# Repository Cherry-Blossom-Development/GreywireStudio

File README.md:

# GreywireStudio

GreywireStudio is a line of guitar effects pedals from Cherry Blossom Development. The first series, **Linework**, is a set of pedals that work on their own or together under a phone-connected control pedal. See `General Concept.docx` for the overall product concept. `Linework Control Specification.docx` defines the rules every Linework pedal follows: the MIDI loop connecting them to Switchyard, the shared message map, presets and firmware updates.

## Tools

All tools are free:

| Tool | Purpose |
|------|---------|
| [KiCad](https://www.kicad.org/) | Schematic capture and PCB layout |
| [LTspice](https://www.analog.com/ltspice) | Circuit simulation (gain, clipping, tone response) |

## Layout

```
libraries/
  GreywireStudio.kicad_sym   # Shared KiCad symbols (e.g. 3PDT footswitch)
pedals/
  <pedal-name>/
    README.md   # Design notes, parts list, status
    *Product Document.docx  # Product definition
    kicad/      # KiCad project (schematic + PCB)
    sim/        # LTspice simulations (.asc)
```

## Pedals

| Pedal | Name | Type | Status |
|-------|------|------|--------|
| [Distortion](pedals/distortion/) | Flashover | Distortion / overdrive | Design |
| [Controller](pedals/controller/) | Switchyard | Control pedal (phone-connected) | Concept |
| [Controller with audio](pedals/controller-audio/) | Switchyard Audio | Control pedal plus digital effects | Planning |
| [Boost](pedals/boost/) | Tap Changer | Clean boost | Design |
| Phaser | Three Phase | Analog phaser | Idea |
| Tremolo | Rolling Blackout | Analog (optical) tremolo | Idea |
| Chorus | Double Circuit | Analog (bucket brigade) chorus / vibrato | Idea |

Product names are working names pending a trademark search (see `IP_RESEARCH.md`).

The public website is https://greywirestudio.com, kept in the [GreywireStudio-Website](https://github.com/Cherry-Blossom-Development/GreywireStudio-Website) repository.

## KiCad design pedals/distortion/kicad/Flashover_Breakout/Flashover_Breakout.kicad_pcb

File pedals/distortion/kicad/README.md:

# Distortion - KiCad Project

Create the KiCad project in this folder (File > New Project in KiCad).

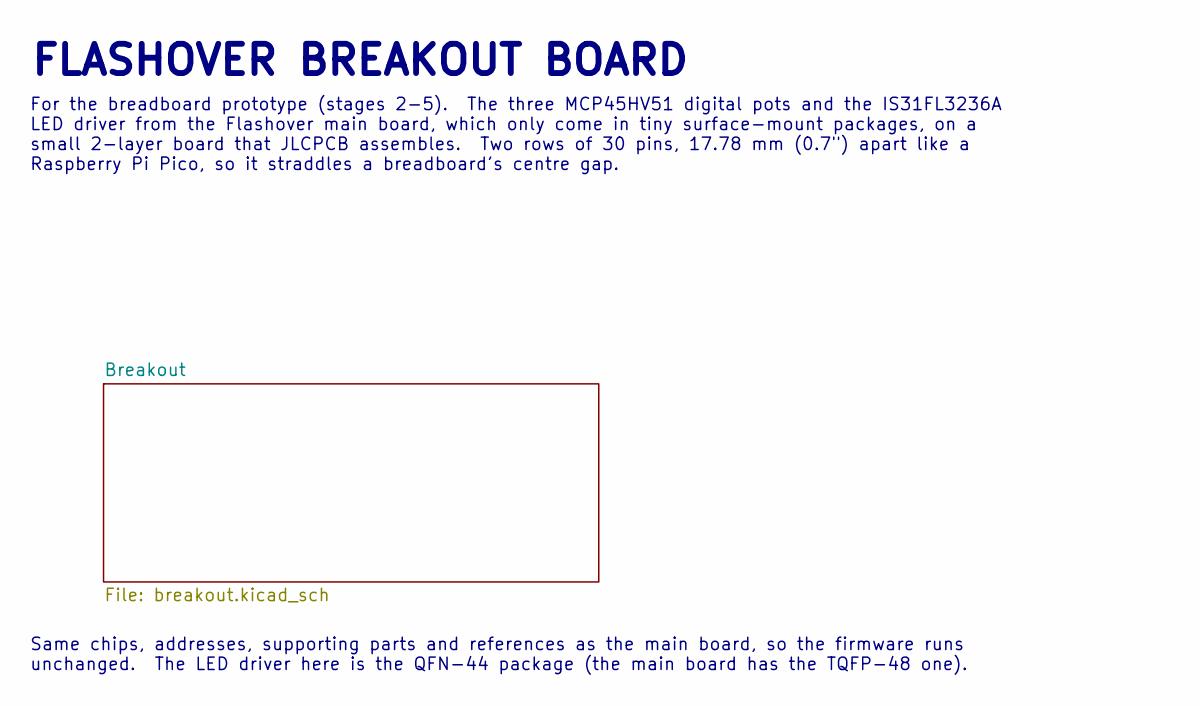
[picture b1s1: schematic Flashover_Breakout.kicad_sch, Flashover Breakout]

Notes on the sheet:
FLASHOVER BREAKOUT BOARD
For the breadboard prototype (stages 2-5). The three MCP45HV51 digital pots and the IS31FL3236A LED driver from the Flashover main board, which only come in tiny surface-mount packages, on a small 2-layer board that JLCPCB assembles. Two rows of 30 pins, 17.78 mm (0.7") apart like a Raspberry Pi Pi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
Same chips, addresses, supporting parts and references as the main board, so the firmware runs unchanged. The LED driver here is the QFN-44 package (the main board has the TQFP-48 one).

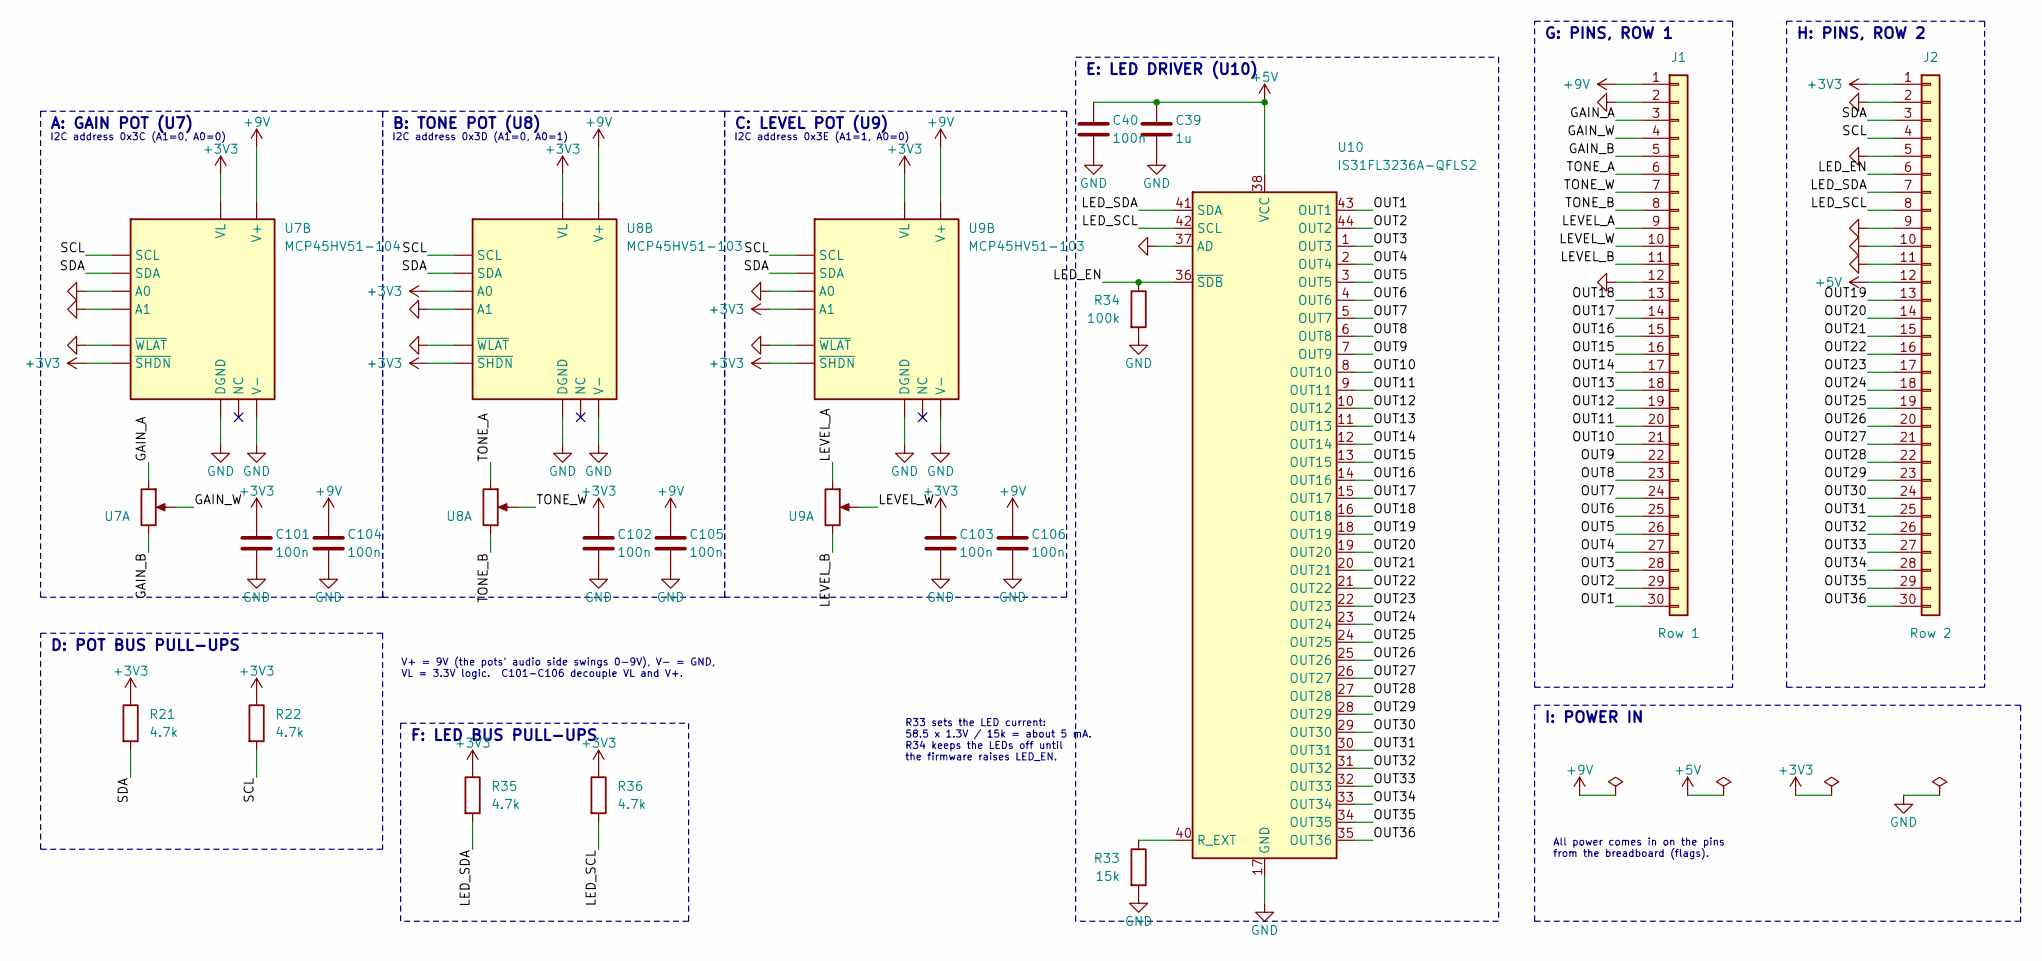
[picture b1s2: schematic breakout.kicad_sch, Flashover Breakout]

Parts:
C39: 1u; C_0603_1608Metric
C40, C101, C102, C103, C104, C105, C106: 100n; C_0603_1608Metric
J1: Row 1; PinHeader_1x30_P2.54mm_Vertical
J2: Row 2; PinHeader_1x30_P2.54mm_Vertical
R21, R22, R35, R36: 4.7k; R_0603_1608Metric
R33: 15k; R_0603_1608Metric
R34: 100k; R_0603_1608Metric
U7: MCP45HV51-104; TSSOP-14_4.4x5mm_P0.65mm
U8, U9: MCP45HV51-103; TSSOP-14_4.4x5mm_P0.65mm
U10: IS31FL3236A-QFLS2; QFN-44-1EP_5x5mm_P0.4mm_EP2.45x2.45mm

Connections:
+3V3: C101.1, C102.1, C103.1, J2.1, R21.1, R22.1, R35.1, R36.1, U7.1 (VL), U7.8 (~SHDN), U8.1 (VL), U8.5 (A0), U8.8 (~SHDN), U9.1 (VL), U9.3 (A1), U9.8 (~SHDN)
+5V: C39.1, C40.1, J2.12, U10.38 (VCC)
+9V: C104.1, C105.1, C106.1, J1.1, U7.14 (V+), U8.14 (V+), U9.14 (V+)
/Breakout/GAIN_A: J1.3, U7.13
/Breakout/GAIN_B: J1.5, U7.11
/Breakout/GAIN_W: J1.4, U7.12
/Breakout/LED_EN: J2.6, R34.1, U10.36 (~SDB)
/Breakout/LED_SCL: J2.8, R36.2, U10.42 (SCL)
/Breakout/LED_SDA: J2.7, R35.2, U10.41 (SDA)
/Breakout/LEVEL_A: J1.9, U9.13
/Breakout/LEVEL_B: J1.11, U9.11
/Breakout/LEVEL_W: J1.10, U9.12
/Breakout/OUT1: J1.30, U10.43 (OUT1)
/Breakout/OUT2: J1.29, U10.44 (OUT2)
/Breakout/OUT3: J1.28, U10.1 (OUT3)
/Breakout/OUT4: J1.27, U10.2 (OUT4)
/Breakout/OUT5: J1.26, U10.3 (OUT5)
/Breakout/OUT6: J1.25, U10.4 (OUT6)
/Breakout/OUT7: J1.24, U10.5 (OUT7)
/Breakout/OUT8: J1.23, U10.6 (OUT8)
/Breakout/OUT9: J1.22, U10.7 (OUT9)
/Breakout/OUT10: J1.21, U10.8 (OUT10)
/Breakout/OUT11: J1.20, U10.9 (OUT11)
/Breakout/OUT12: J1.19, U10.10 (OUT12)
/Breakout/OUT13: J1.18, U10.11 (OUT13)
/Breakout/OUT14: J1.17, U10.12 (OUT14)
/Breakout/OUT15: J1.16, U10.13 (OUT15)
/Breakout/OUT16: J1.15, U10.14 (OUT16)
/Breakout/OUT17: J1.14, U10.15 (OUT17)
/Breakout/OUT18: J1.13, U10.16 (OUT18)
/Breakout/OUT19: J2.13, U10.18 (OUT19)
/Breakout/OUT20: J2.14, U10.19 (OUT20)
/Breakout/OUT21: J2.15, U10.20 (OUT21)
/Breakout/OUT22: J2.16, U10.21 (OUT22)
/Breakout/OUT23: J2.17, U10.22 (OUT23)
/Breakout/OUT24: J2.18, U10.23 (OUT24)
/Breakout/OUT25: J2.19, U10.24 (OUT25)
/Breakout/OUT26: J2.20, U10.25 (OUT26)
/Breakout/OUT27: J2.21, U10.26 (OUT27)
/Breakout/OUT28: J2.22, U10.27 (OUT28)
/Breakout/OUT29: J2.23, U10.28 (OUT29)
/Breakout/OUT30: J2.24, U10.29 (OUT30)
/Breakout/OUT31: J2.25, U10.30 (OUT31)
/Breakout/OUT32: J2.26, U10.31 (OUT32)
/Breakout/OUT33: J2.27, U10.32 (OUT33)
/Breakout/OUT34: J2.28, U10.33 (OUT34)
/Breakout/OUT35: J2.29, U10.34 (OUT35)
/Breakout/OUT36: J2.30, U10.35 (OUT36)
/Breakout/SCL: J2.4, R22.2, U7.2 (SCL), U8.2 (SCL), U9.2 (SCL)
/Breakout/SDA: J2.3, R21.2, U7.4 (SDA), U8.4 (SDA), U9.4 (SDA)
/Breakout/TONE_A: J1.6, U8.13
/Breakout/TONE_B: J1.8, U8.11
/Breakout/TONE_W: J1.7, U8.12
GND: C39.2, C40.2, C101.2, C102.2, C103.2, C104.2, C105.2, C106.2, J1.2, J1.12, J2.2, J2.5, J2.9, J2.10, J2.11, R33.2, R34.2, U7.3 (A1), U7.5 (A0), U7.6 (~WLAT), U7.9 (DGND), U7.10 (V-), U8.3 (A1), U8.6 (~WLAT), U8.9 (DGND), U8.10 (V-), U9.5 (A0), U9.6 (~WLAT), U9.9 (DGND), U9.10 (V-), U10.17 (GND), U10.37 (AD), U10.39 (GND), U10.45 (GND)
unnamed: R33.1, U10.40 (R_EXT)

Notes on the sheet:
A: GAIN POT (U7)
I2C address 0x3C (A1=0, A0=0)
B: TONE POT (U8)
I2C address 0x3D (A1=0, A0=1)
C: LEVEL POT (U9)
I2C address 0x3E (A1=1, A0=0)
D: POT BUS PULL-UPS
V+ = 9V (the pots' audio side swings 0-9V), V- = GND, VL = 3.3V logic. C101-C106 decouple VL and V+.
E: LED DRIVER (U10)
R33 sets the LED current: 58.5 x 1.3V / 15k = about 5 mA. R34 keeps the LEDs off until the firmware raises LED_EN.
F: LED BUS PULL-UPS
G: PINS, ROW 1
H: PINS, ROW 2
I: POWER IN
All power comes in on the pins from the breadboard (flags).

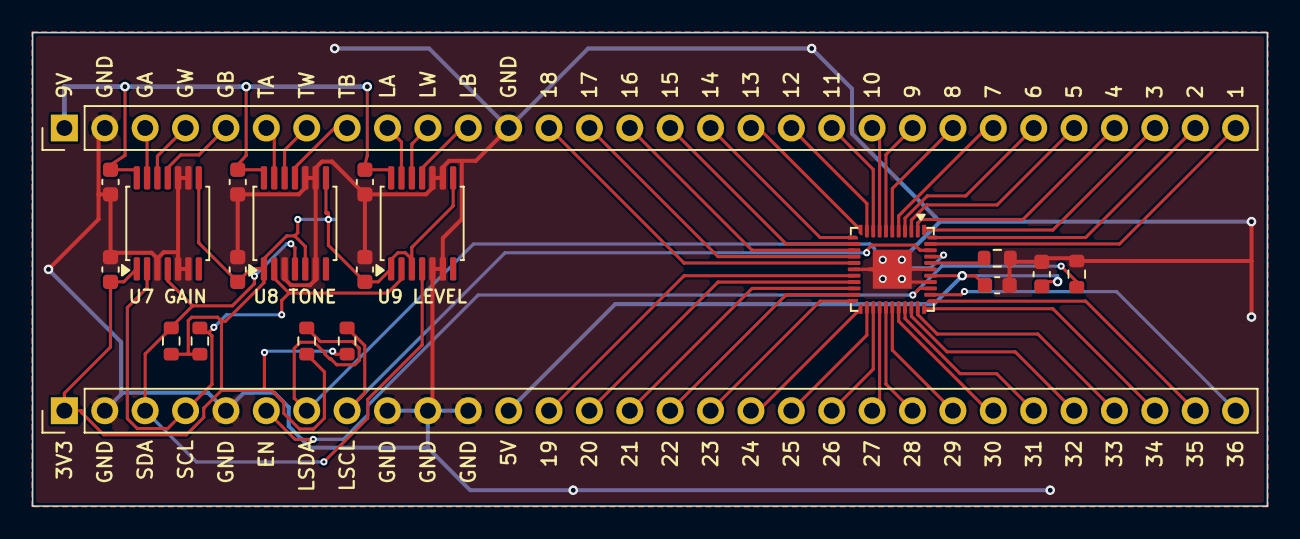
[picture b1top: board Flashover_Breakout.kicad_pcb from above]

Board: 2 copper layers, 77.7 x 29.8 mm, 20 parts (0 on the bottom side), 55 nets.

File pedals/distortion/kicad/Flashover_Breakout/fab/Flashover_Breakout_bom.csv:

Comment,Designator,Footprint,LCSC Part #
100k 1% 0603,R34,R_0603_1608Metric,C25803
100nF 50V X7R 0603,"C40,C101,C102,C103,C104,C105,C106",C_0603_1608Metric,C14663
15k 1% 0603,R33,R_0603_1608Metric,C22809
1uF 25V X5R 0603,C39,C_0603_1608Metric,C15849
4.7k 1% 0603,"R21,R22,R35,R36",R_0603_1608Metric,C23162
IS31FL3236A-QFLS2-TR,U10,QFN-44-1EP_5x5mm_P0.4mm_EP2.45x2.45mm,C246443
MCP45HV51-103E/ST,"U8,U9",TSSOP-14_4.4x5mm_P0.65mm,C637117
MCP45HV51-104E/ST,U7,TSSOP-14_4.4x5mm_P0.65mm,C637118

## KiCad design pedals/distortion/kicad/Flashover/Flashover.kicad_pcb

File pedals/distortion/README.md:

# Distortion Pedal (Flashover)

The first GreywireStudio pedal: an analog distortion / overdrive in the Linework series, with gain, tone and level controls. It works on its own or controlled by the Switchyard control pedal. See `Flashover Product Document.docx`.

The design files still use the internal name GS1.

## Folders

- `kicad/` - KiCad project (schematic and PCB layout)
- `sim/` - LTspice simulations of the circuit
- `firmware/` - firmware for the RP2040 (started November 2026; not yet run on hardware)

## Status

Design - circuit not yet started.

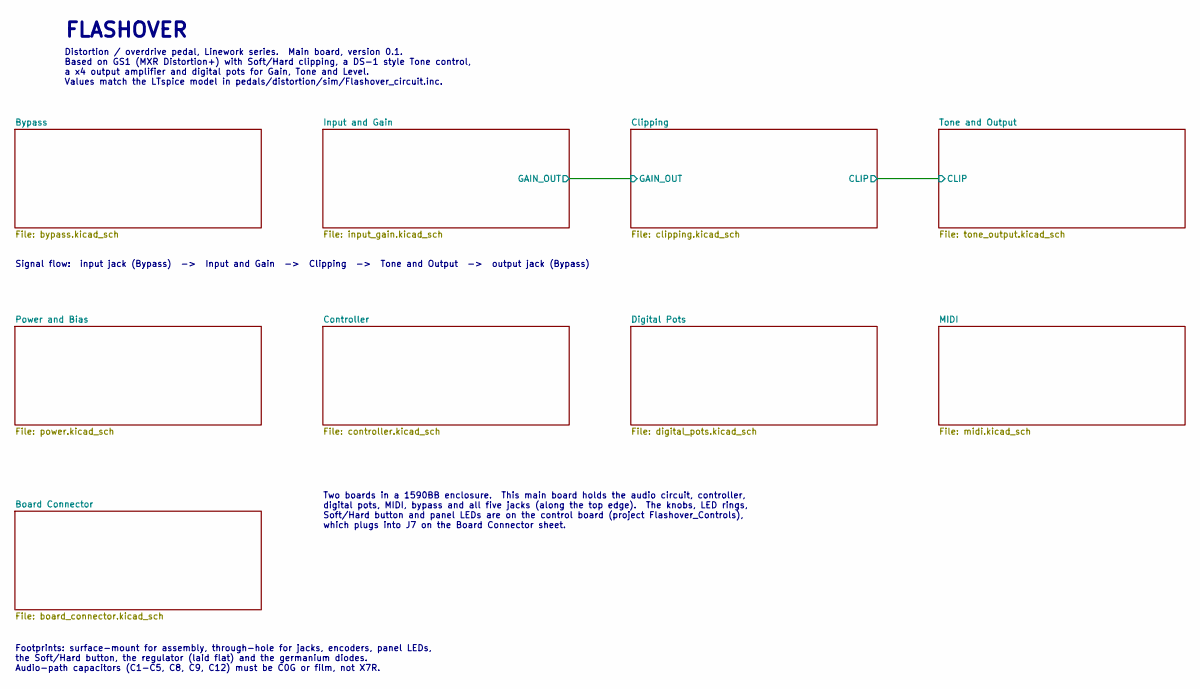
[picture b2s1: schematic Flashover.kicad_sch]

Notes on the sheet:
FLASHOVER
Distortion / overdrive pedal, Linework series. Main board, version 0.1. Based on GS1 (MXR Distortion+) with Soft/Hard clipping, a DS-1 style Tone control, a x4 output amplifier and digital pots for Gain, Tone and Level. Values match the LTspice model in pedals/distortion/sim/Flashover_circuit.inc.
Signal flow: input jack (Bypass) -> Input and Gain -> Clipping -> Tone and Output -> output jack (Bypass)
Two boards in a 1590BB enclosure. This main board holds the audio circuit, controller, digital pots, MIDI, bypass and all five jacks (along the top edge). The knobs, LED rings, Soft/Hard button and panel LEDs are on the control board (project Flashover_Controls), which plugs into J7 on the Board Co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
Footprints: surface-mount for assembly, through-hole for jacks, encoders, panel LEDs, the Soft/Hard button, the regulator (laid flat) and the germanium diodes. Audio-path capacitors (C1-C5, C8, C9, C12) must be C0G or film, not X7R.

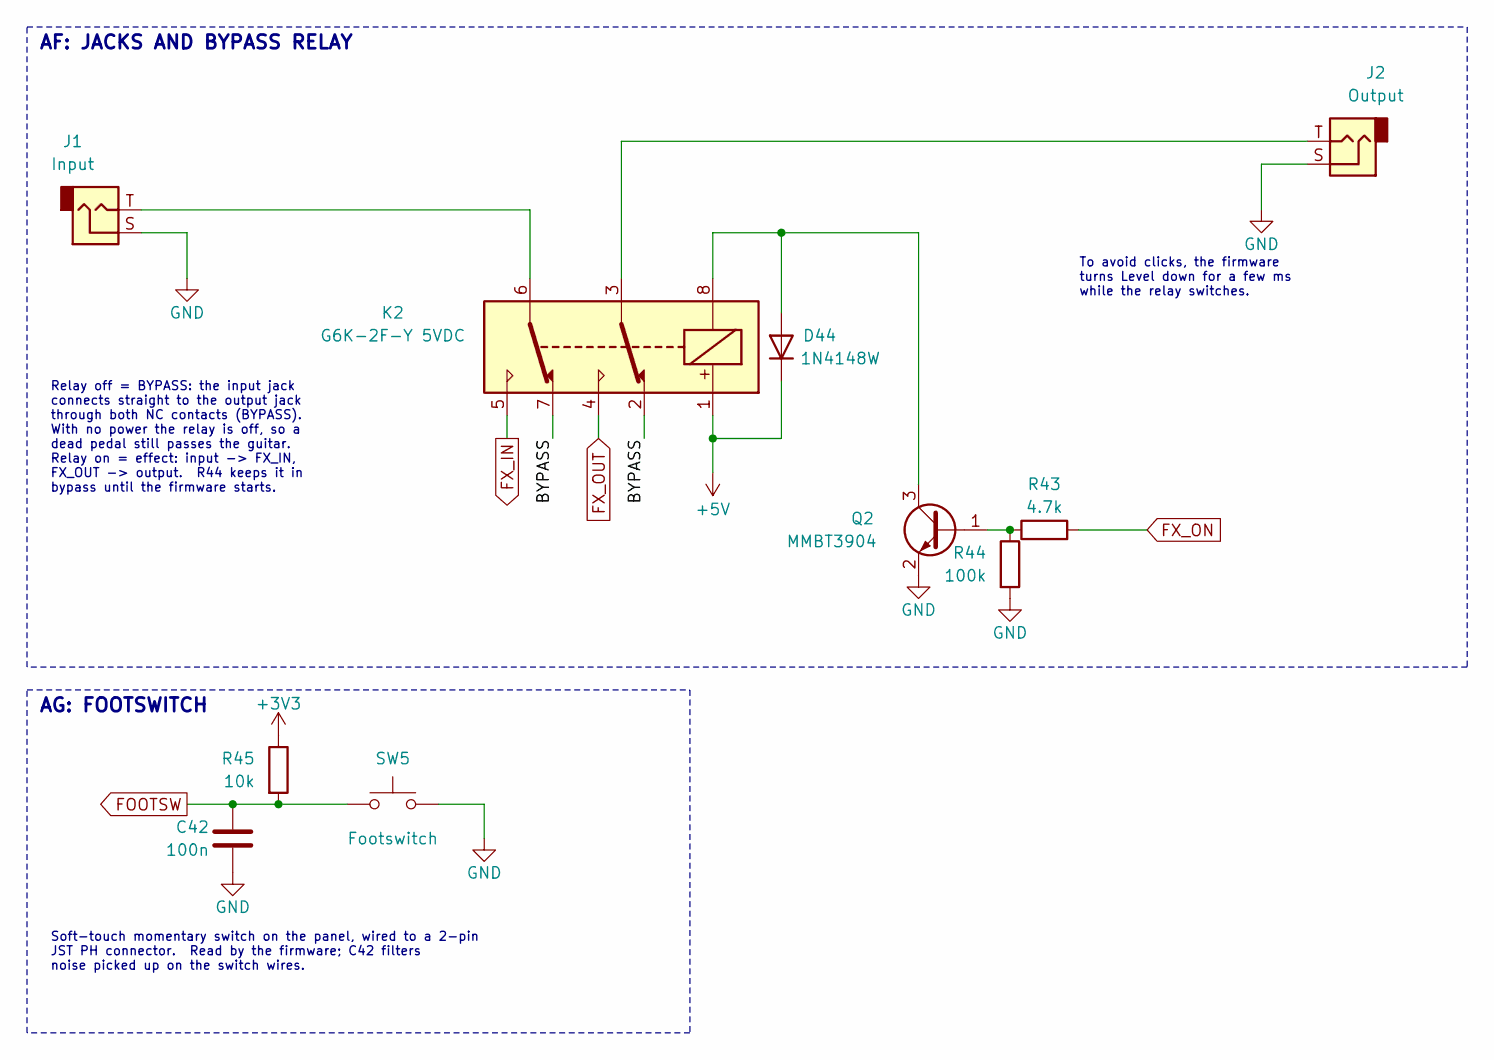
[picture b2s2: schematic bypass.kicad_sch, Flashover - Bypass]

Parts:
C42: 100n; C_0805_2012Metric
D44: 1N4148W; D_SOD-123
J1: Input; Jack_6.35mm_Neutrik_NRJ4HF_Horizontal
J2: Output; Jack_6.35mm_Neutrik_NRJ4HF_Horizontal
K2: G6K-2F-Y 5VDC; Relay_DPDT_Omron_G6K-2F-Y
Q2: MMBT3904; SOT-23
R43: 4.7k; R_0805_2012Metric
R44: 100k; R_0805_2012Metric
R45: 10k; R_0805_2012Metric
SW5: Footswitch; JST_PH_S2B-PH-K_1x02_P2.00mm_Horizontal

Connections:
+3V3: R45.1; also elsewhere on the board
+5V: D44.1 (K), K2.1; also elsewhere on the board
/Bypass/BYPASS: K2.2, K2.7
FOOTSW: C42.1, R45.2, SW5.1; also elsewhere on the board
FX_IN: K2.5; also elsewhere on the board
FX_ON: R43.2; also elsewhere on the board
FX_OUT: K2.4; also elsewhere on the board
GND: C42.2, J1.S, J2.S, Q2.2 (E), R44.2, SW5.2; also elsewhere on the board
unnamed: D44.2 (A), K2.8, Q2.3 (C)
unnamed: J1.T, K2.6
unnamed: J2.T, K2.3
unnamed: Q2.1 (B), R43.1, R44.1

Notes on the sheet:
AF: JACKS AND BYPASS RELAY
AG: FOOTSWITCH
Relay off = BYPASS: the input jack connects straight to the output jack through both NC contacts (BYPASS). With no power the relay is off, so a dead pedal still passes the guitar. Relay on = effect: input -> FX_IN, FX_OUT -> output. R44 keeps it in bypass until the firmware starts.
To avoid clicks, the firmware turns Level down for a few ms while the relay switches.
Soft-touch momentary switch on the panel, wired to a 2-pin JST PH connector. Read by the firmware; C42 filters noise picked up on the switch wires.

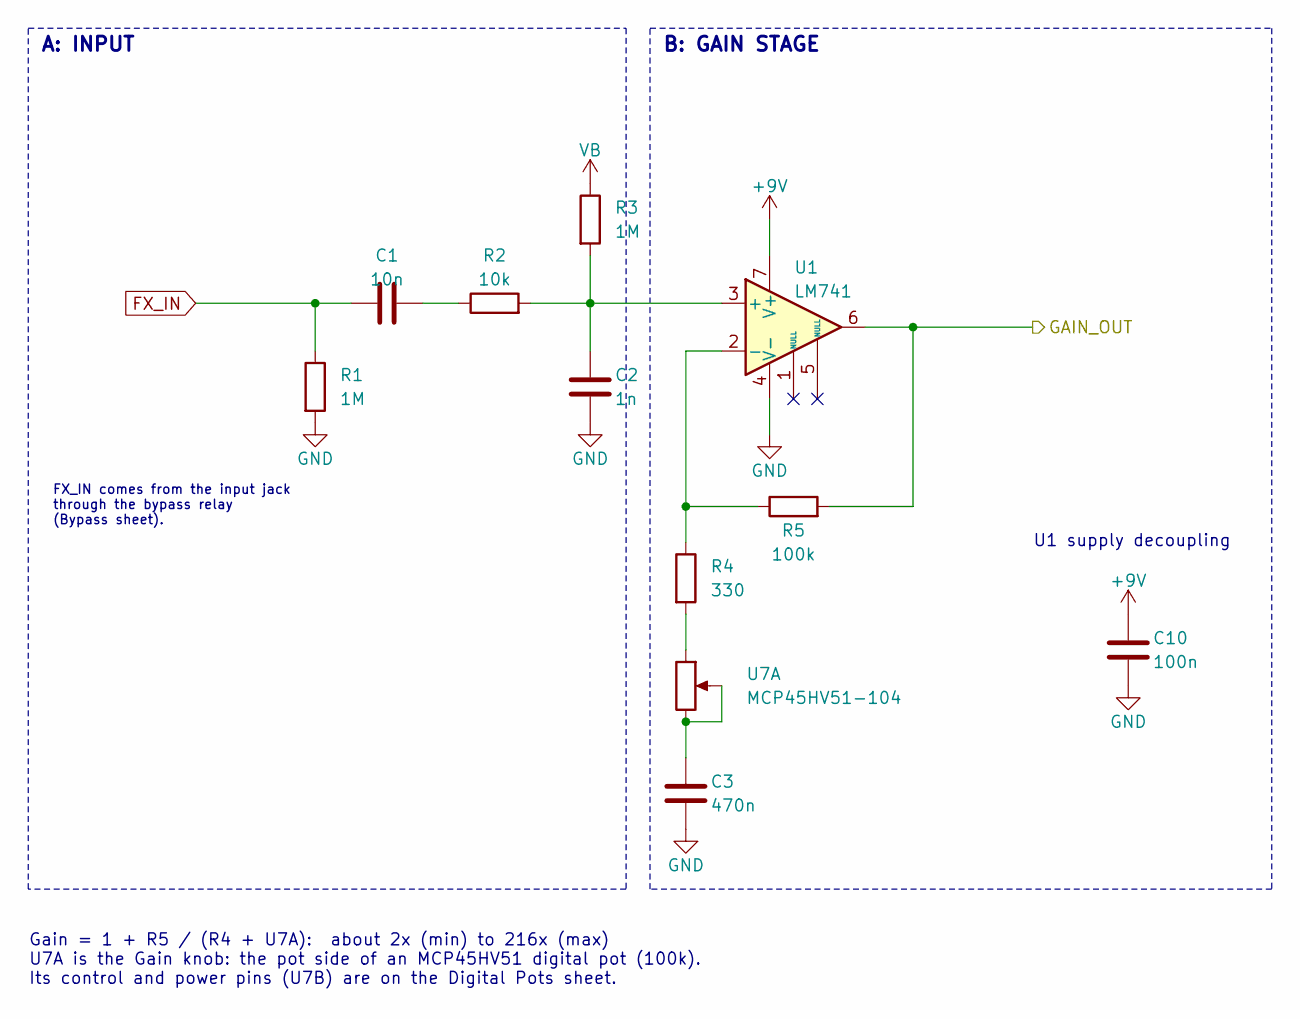
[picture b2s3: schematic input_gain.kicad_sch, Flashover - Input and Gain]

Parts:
C1: 10n; C_1206_3216Metric
C2: 1n; C_0805_2012Metric
C3: 470n; C_1210_3225Metric
C10: 100n; C_0805_2012Metric
R1, R3: 1M; R_0805_2012Metric
R2: 10k; R_0805_2012Metric
R4: 330; R_0805_2012Metric
R5: 100k; R_0805_2012Metric
U1: LM741; SOIC-8_3.9x4.9mm_P1.27mm
U7: MCP45HV51-104; TSSOP-14_4.4x5mm_P0.65mm

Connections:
+9V: C10.1, U1.7 (V+); also elsewhere on the board
/Clipping/GAIN_OUT: R5.2, U1.6; also elsewhere on the board
FX_IN: C1.1, R1.1; also elsewhere on the board
GND: C2.2, C3.2, C10.2, R1.2, U1.4 (V-); also elsewhere on the board
unnamed: C1.2, R2.1
unnamed: C3.1, U7.11, U7.12
unnamed: R4.2, U7.13
unnamed: C2.1, R2.2, R3.2, U1.3 (+)
unnamed: R4.1, R5.1, U1.2 (-)
VB: R3.1; also elsewhere on the board

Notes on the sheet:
A: INPUT
B: GAIN STAGE
FX_IN comes from the input jack through the bypass relay (Bypass sheet).
U1 supply decoupling
Gain = 1 + R5 / (R4 + U7A): about 2x (min) to 216x (max) U7A is the Gain knob: the pot side of an MCP45HV51 digital pot (100k). Its control and power pins (U7B) are on the Digital Pots sheet.

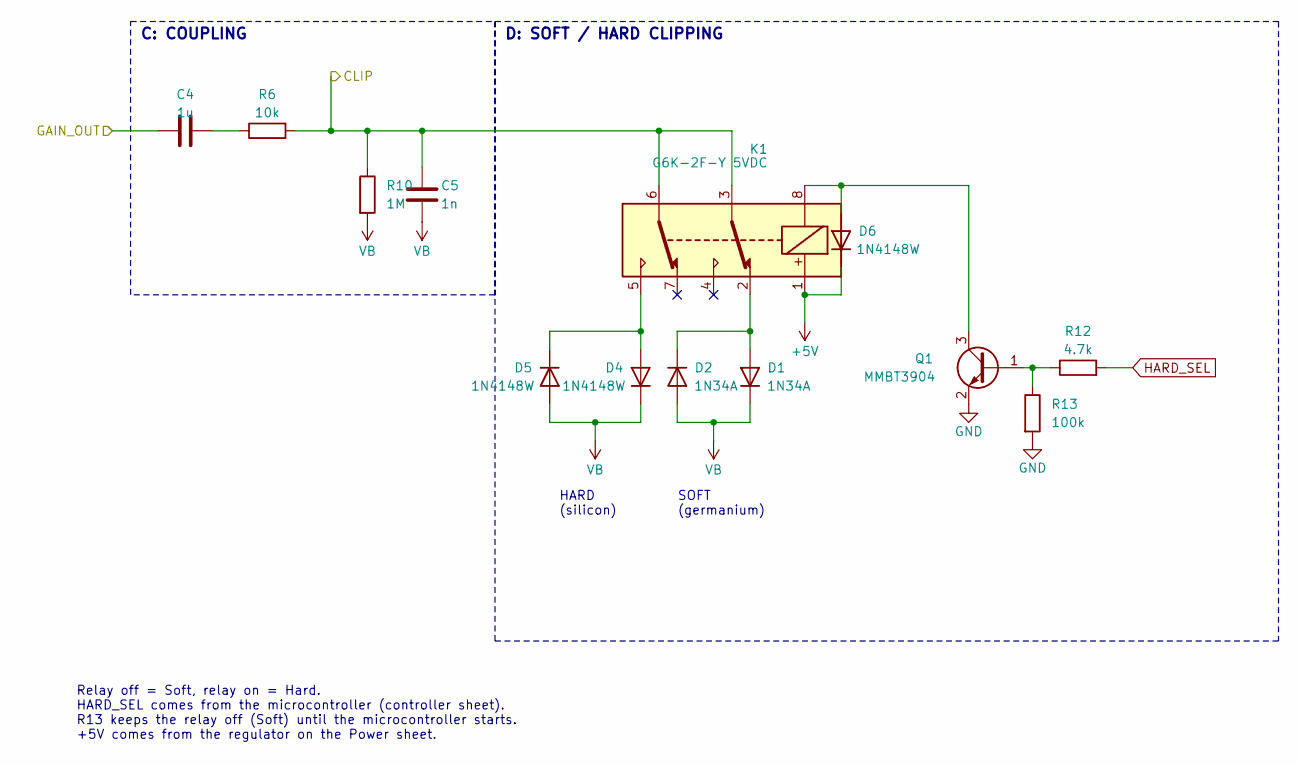
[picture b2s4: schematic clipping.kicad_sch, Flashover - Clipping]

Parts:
C4: 1u; C_1210_3225Metric
C5: 1n; C_0805_2012Metric
D1, D2: 1N34A; D_DO-35_SOD27_P7.62mm_Horizontal
D4, D5, D6: 1N4148W; D_SOD-123
K1: G6K-2F-Y 5VDC; Relay_DPDT_Omron_G6K-2F-Y
Q1: MMBT3904; SOT-23
R6: 10k; R_0805_2012Metric
R10: 1M; R_0805_2012Metric
R12: 4.7k; R_0805_2012Metric
R13: 100k; R_0805_2012Metric

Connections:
+5V: D6.1 (K), K1.1; also elsewhere on the board
/Clipping/CLIP: C5.1, K1.3, K1.6, R6.2, R10.1; also elsewhere on the board
/Clipping/GAIN_OUT: C4.1; also elsewhere on the board
GND: Q1.2 (E), R13.2; also elsewhere on the board
HARD_SEL: R12.2; also elsewhere on the board
unnamed: C4.2, R6.1
unnamed: D1.2 (A), D2.1 (K), K1.2
unnamed: D4.2 (A), D5.1 (K), K1.5
unnamed: D6.2 (A), K1.8, Q1.3 (C)
unnamed: Q1.1 (B), R12.1, R13.1
VB: C5.2, D1.1 (K), D2.2 (A), D4.1 (K), D5.2 (A), R10.2; also elsewhere on the board

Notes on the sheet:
C: COUPLING
D: SOFT / HARD CLIPPING
SOFT (germanium)
HARD (silicon)
Relay off = Soft, relay on = Hard. HARD_SEL comes from the microcontroller (controller sheet). R13 keeps the relay off (Soft) until the microcontroller starts. +5V comes from the regulator on the Power sheet.

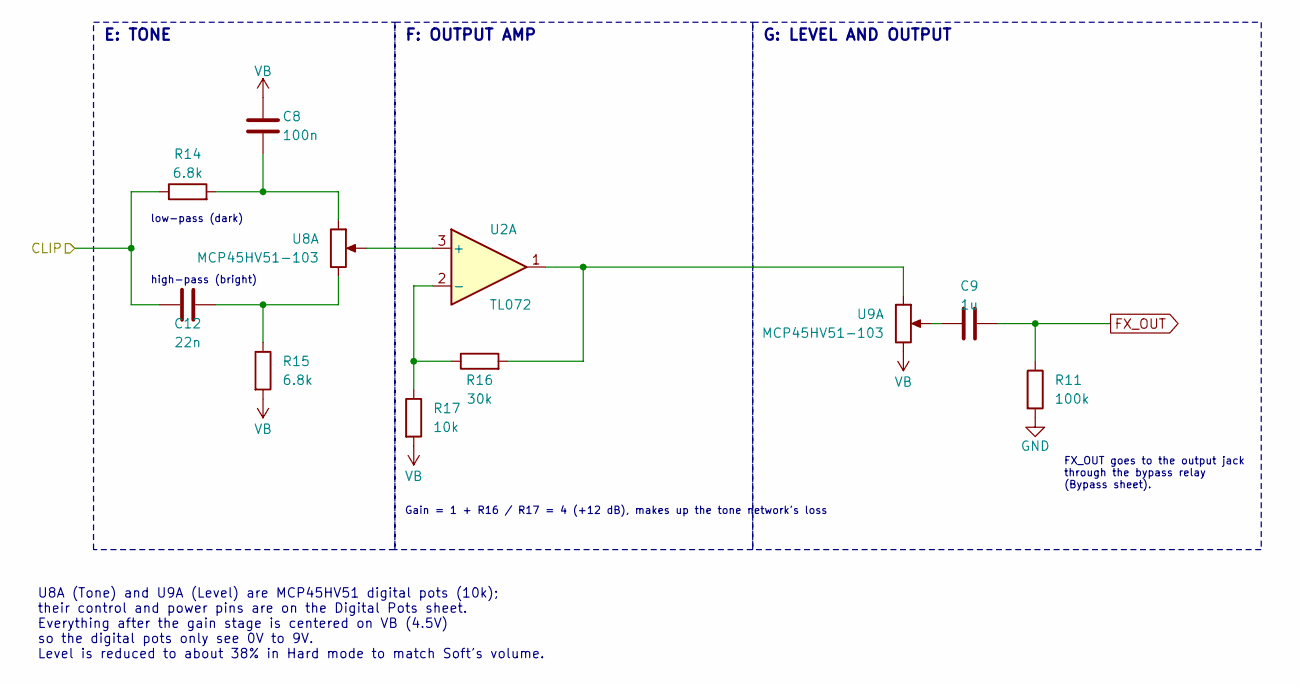
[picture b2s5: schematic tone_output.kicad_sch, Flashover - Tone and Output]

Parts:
C8: 100n; C_1206_3216Metric
C9: 1u; C_1210_3225Metric
C12: 22n; C_1206_3216Metric
R11: 100k; R_0805_2012Metric
R14, R15: 6.8k; R_0805_2012Metric
R16: 30k; R_0805_2012Metric
R17: 10k; R_0805_2012Metric
U2: TL072; SOIC-8_3.9x4.9mm_P1.27mm
U8, U9: MCP45HV51-103; TSSOP-14_4.4x5mm_P0.65mm

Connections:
/Clipping/CLIP: C12.1, R14.1; also elsewhere on the board
FX_OUT: C9.2, R11.1; also elsewhere on the board
GND: R11.2; also elsewhere on the board
unnamed: C8.2, R14.2, U8.13
unnamed: C9.1, U9.12
unnamed: C12.2, R15.1, U8.11
unnamed: R16.2, U2.1, U9.13
unnamed: U2.3 (+), U8.12
unnamed: R16.1, R17.1, U2.2 (-)
VB: C8.1, R15.2, R17.2, U9.11; also elsewhere on the board

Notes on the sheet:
E: TONE
F: OUTPUT AMP
G: LEVEL AND OUTPUT
low-pass (dark)
high-pass (bright)
FX_OUT goes to the output jack through the bypass relay (Bypass sheet).
Gain = 1 + R16 / R17 = 4 (+12 dB), makes up the tone network's loss
U8A (Tone) and U9A (Level) are MCP45HV51 digital pots (10k); their control and power pins are on the Digital Pots sheet. Everything after the gain stage is centered on VB (4.5V) so the digital pots only see 0V to 9V. Level is reduced to about 38% in Hard mode to match Soft's volume.

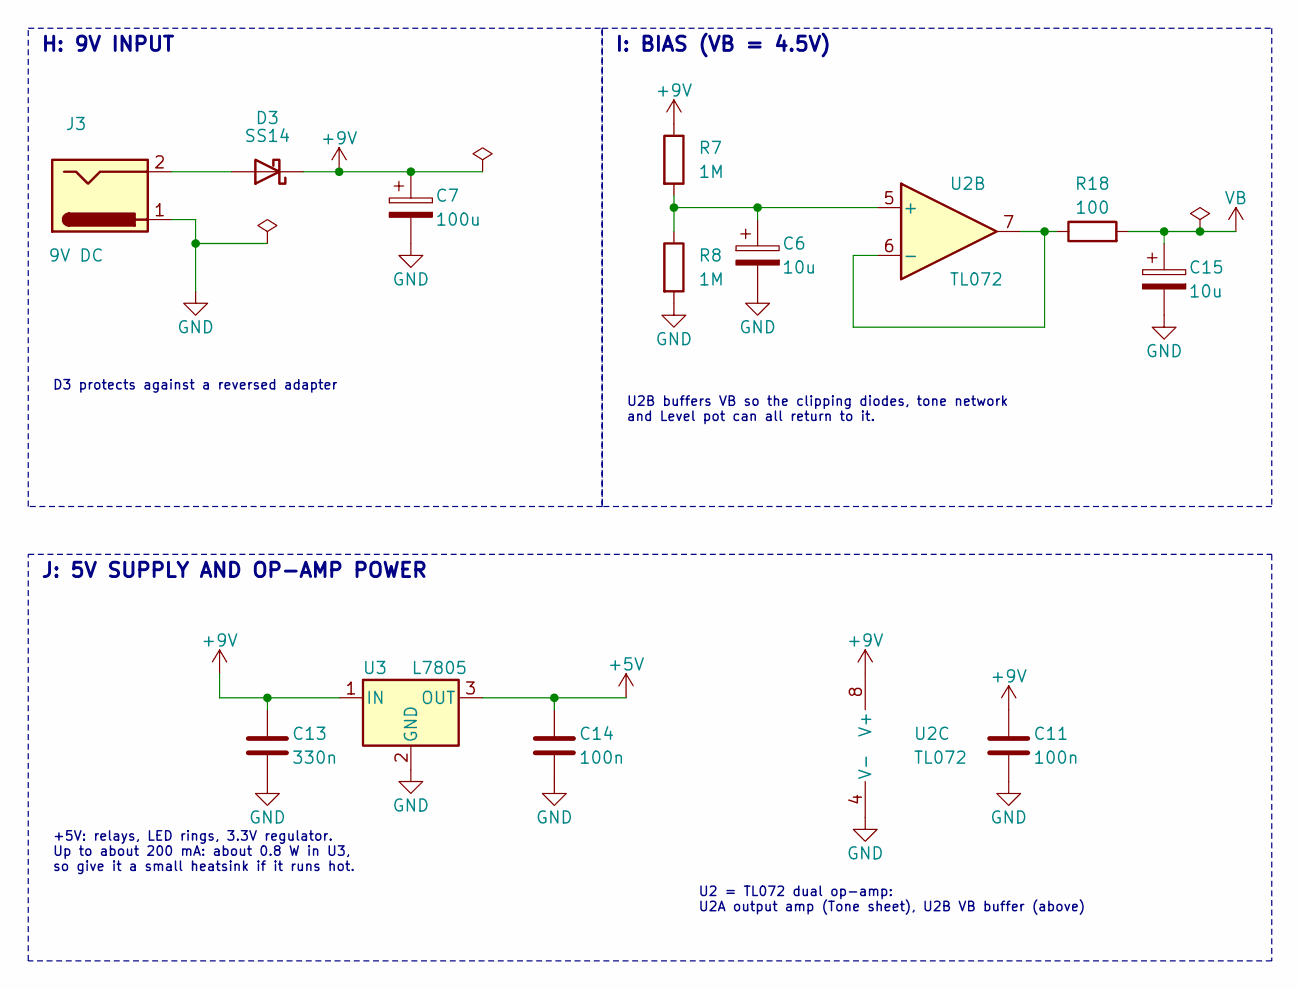
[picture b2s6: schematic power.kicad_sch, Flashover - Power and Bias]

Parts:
C6, C15: 10u; CP_Elec_5x5.4
C7: 100u; CP_Elec_6.3x5.4
C11, C14: 100n; C_0805_2012Metric
C13: 330n; C_0805_2012Metric
D3: SS14; D_SMA
J3: 9V DC; BarrelJack_CUI_PJ-102AH_Horizontal
R7, R8: 1M; R_0805_2012Metric
R18: 100; R_0805_2012Metric
U2: TL072; SOIC-8_3.9x4.9mm_P1.27mm
U3: L7805; TO-220-3_Horizontal_TabDown

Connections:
+5V: C14.1, U3.3 (OUT); also elsewhere on the board
+9V: C7.1, C11.1, C13.1, D3.1 (K), R7.1, U2.8 (V+), U3.1 (IN); also elsewhere on the board
GND: C6.2, C7.2, C11.2, C13.2, C14.2, C15.2, J3.1, R8.2, U2.4 (V-), U3.2 (GND); also elsewhere on the board
unnamed: D3.2 (A), J3.2
unnamed: C6.1, R7.2, R8.1, U2.5 (+)
unnamed: R18.1, U2.6 (-), U2.7
VB: C15.1, R18.2; also elsewhere on the board

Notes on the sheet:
H: 9V INPUT
I: BIAS (VB = 4.5V)
J: 5V SUPPLY AND OP-AMP POWER
D3 protects against a reversed adapter
U2B buffers VB so the clipping diodes, tone network and Level pot can all return to it.
+5V: relays, LED rings, 3.3V regulator. Up to about 200 mA: about 0.8 W in U3, so give it a small heatsink if it runs hot.
U2 = TL072 dual op-amp: U2A output amp (Tone sheet), U2B VB buffer (above)

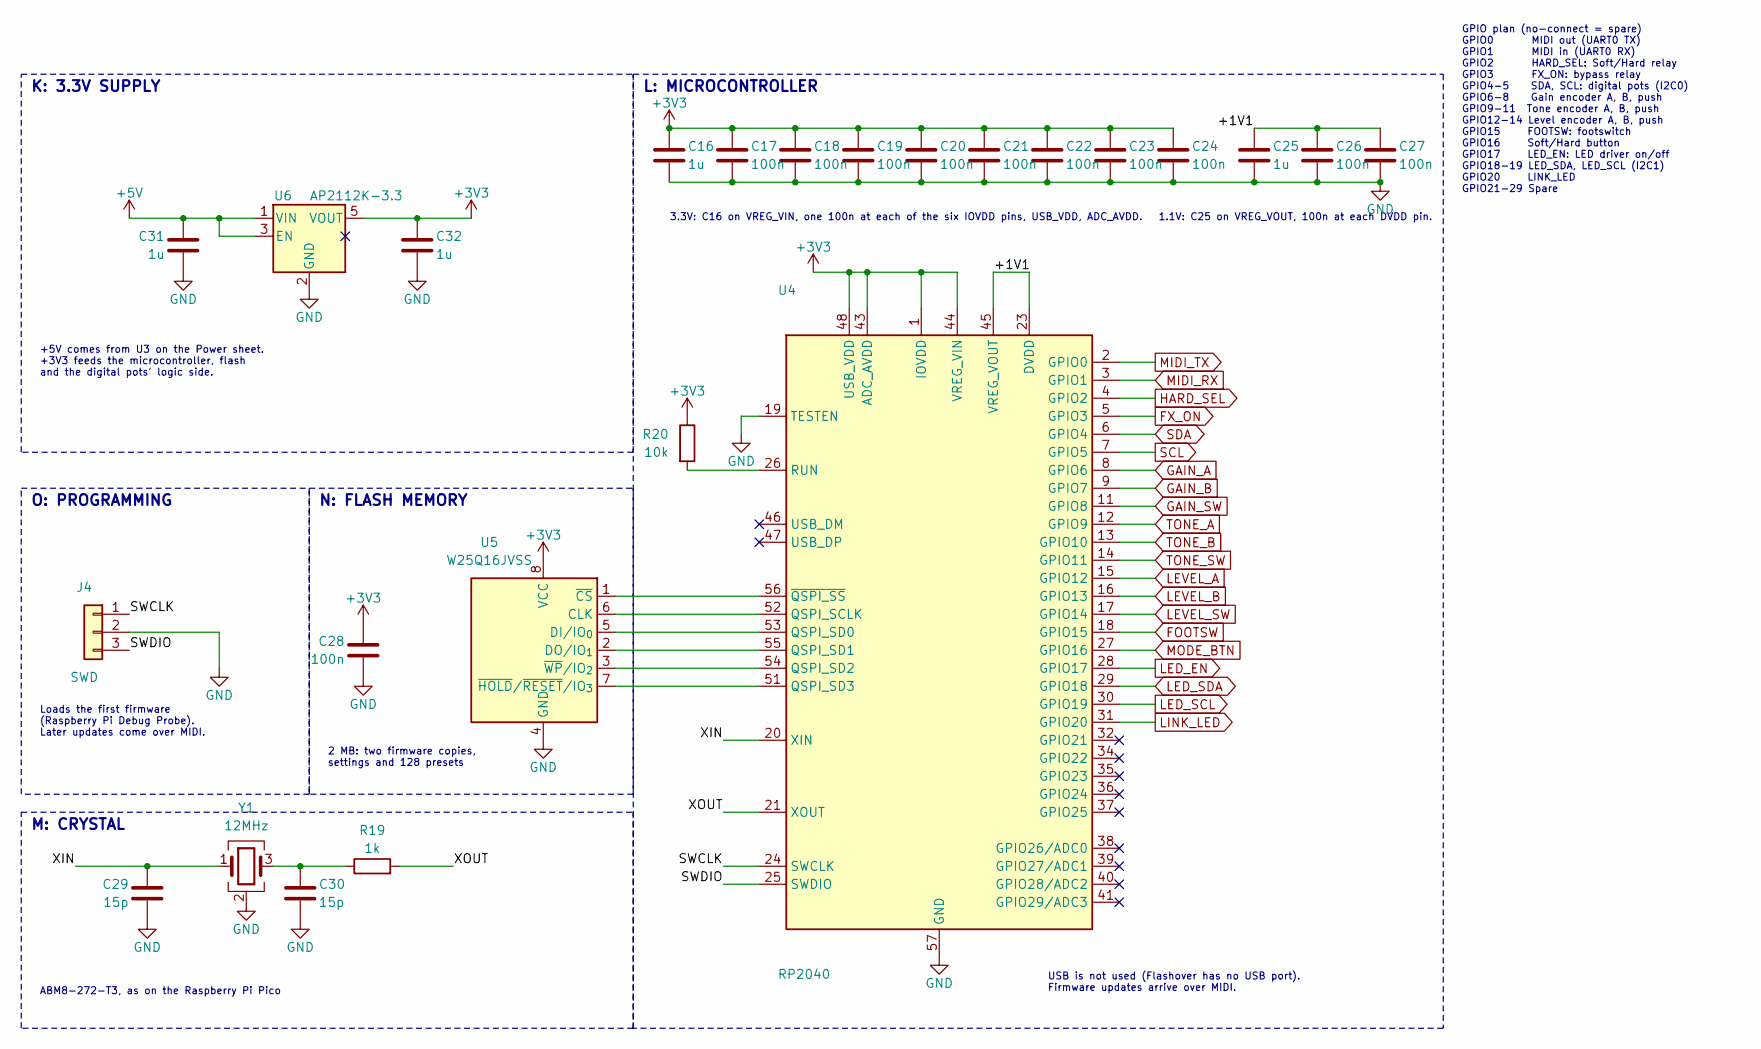
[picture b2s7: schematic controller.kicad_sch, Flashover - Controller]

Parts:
C16, C25, C31, C32: 1u; C_0805_2012Metric
C17, C18, C19, C20, C21, C22, C23, C24, C26, C27, C28: 100n; C_0805_2012Metric
C29, C30: 15p; C_0805_2012Metric
J4: SWD; JST_SH_SM03B-SRSS-TB_1x03-1MP_P1.00mm_Horizontal
R19: 1k; R_0805_2012Metric
R20: 10k; R_0805_2012Metric
U4: RP2040; QFN-56-1EP_7x7mm_P0.4mm_EP3.2x3.2mm
U5: W25Q16JVSS; SOIC-8_5.3x5.3mm_P1.27mm
U6: AP2112K-3.3; SOT-23-5
Y1: 12MHz; Crystal_SMD_3225-4Pin_3.2x2.5mm

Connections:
+3V3: C16.1, C17.1, C18.1, C19.1, C20.1, C21.1, C22.1, C23.1, C24.1, C28.1, C32.1, R20.1, U4.1 (IOVDD), U4.10 (IOVDD), U4.22 (IOVDD), U4.33 (IOVDD), U4.42 (IOVDD), U4.43 (ADC_AVDD), U4.44 (VREG_VIN), U4.48 (USB_VDD), U4.49 (IOVDD), U5.8 (VCC), U6.5 (VOUT); also elsewhere on the board
+5V: C31.1, U6.1 (VIN), U6.3 (EN); also elsewhere on the board
/Controller/+1V1: C25.1, C26.1, C27.1, U4.23 (DVDD), U4.45 (VREG_VOUT), U4.50 (DVDD)
/Controller/SWCLK: J4.1, U4.24 (SWCLK)
/Controller/SWDIO: J4.3, U4.25 (SWDIO)
/Controller/XIN: C29.1, U4.20 (XIN), Y1.1
/Controller/XOUT: R19.2, U4.21 (XOUT)
FOOTSW: U4.18 (GPIO15); also elsewhere on the board
FX_ON: U4.5 (GPIO3); also elsewhere on the board
GAIN_A: U4.8 (GPIO6); also elsewhere on the board
GAIN_B: U4.9 (GPIO7); also elsewhere on the board
GAIN_SW: U4.11 (GPIO8); also elsewhere on the board
GND: C16.2, C17.2, C18.2, C19.2, C20.2, C21.2, C22.2, C23.2, C24.2, C25.2, C26.2, C27.2, C28.2, C29.2, C30.2, C31.2, C32.2, J4.2, U4.19 (TESTEN), U4.57 (GND), U5.4 (GND), U6.2 (GND), Y1.2 (G), Y1.4 (G); also elsewhere on the board
HARD_SEL: U4.4 (GPIO2); also elsewhere on the board
LED_EN: U4.28 (GPIO17); also elsewhere on the board
LED_SCL: U4.30 (GPIO19); also elsewhere on the board
LED_SDA: U4.29 (GPIO18); also elsewhere on the board
LEVEL_A: U4.15 (GPIO12); also elsewhere on the board
LEVEL_B: U4.16 (GPIO13); also elsewhere on the board
LEVEL_SW: U4.17 (GPIO14); also elsewhere on the board
LINK_LED: U4.31 (GPIO20); also elsewhere on the board
MIDI_RX: U4.3 (GPIO1); also elsewhere on the board
MIDI_TX: U4.2 (GPIO0); also elsewhere on the board
MODE_BTN: U4.27 (GPIO16); also elsewhere on the board
unnamed: C30.1, R19.1, Y1.3
unnamed: U4.52 (QSPI_SCLK), U5.6 (CLK)
unnamed: U4.53 (QSPI_SD0), U5.5 (DI/IO_{0})
unnamed: U4.55 (QSPI_SD1), U5.2 (DO/IO_{1})
unnamed: U4.54 (QSPI_SD2), U5.3 (~WP/IO_{2})
unnamed: U4.51 (QSPI_SD3), U5.7 (~HOLD/~RESET/IO_{3})
unnamed: R20.2, U4.26 (RUN)
unnamed: U4.56 (~QSPI_SS), U5.1 (~CS)
SCL: U4.7 (GPIO5); also elsewhere on the board
SDA: U4.6 (GPIO4); also elsewhere on the board
TONE_A: U4.12 (GPIO9); also elsewhere on the board
TONE_B: U4.13 (GPIO10); also elsewhere on the board
TONE_SW: U4.14 (GPIO11); also elsewhere on the board

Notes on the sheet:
K: 3.3V SUPPLY
L: MICROCONTROLLER
O: PROGRAMMING
N: FLASH MEMORY
M: CRYSTAL
+5V comes from U3 on the Power sheet. +3V3 feeds the microcontroller, flash and the digital pots' logic side.
3.3V: C16 on VREG_VIN, one 100n at each of the six IOVDD pins, USB_VDD, ADC_AVDD. 1.1V: C25 on VREG_VOUT, 100n at each DVDD pin.
GPIO plan (no-connect = spare) GPIO0 MIDI out (UART0 TX) GPIO1 MIDI in (UART0 RX) GPIO2 HARD_SEL: Soft/Hard relay GPIO3 FX_ON: bypass relay GPIO4-5 SDA, SCL: digital pots (I2C0) GPIO6-8 Gain encoder A, B, push GPIO9-11 Tone encoder A, B, push GPIO12-14 Level encoder A, B, push GPIO15 FOOTSW: footsw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
USB is not used (Flashover has no USB port). Firmware updates arrive over MIDI.
2 MB: two firmware copies, settings and 128 presets
ABM8-272-T3, as on the Raspberry Pi Pico
Loads the first firmware (Raspberry Pi Debug Probe). Later updates come over MIDI.
